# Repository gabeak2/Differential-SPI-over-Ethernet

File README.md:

# Differential-SPI-over-Ethernet
The board is meant to drive 2 SPI channels differentially over ethernet cables, and plugs into those "PMOD" connectors that all the FPGA dev boards have (but they are just 6x2 R/A 100mil headers, so also compatible with dupont/breadboard wires).  Right now I have one SPI channel with 500kHz slew-rate-limited transceivers stuffed, and one with 15MHz ones, but the chips have an identical SOIC-8 footprint so it's just a BOM change to swap them around whichever way you like.  There are solder jumpers on the board that let you hook the transceivers up so that it works for either the host side or the client side (clk is an output on a SPI host, but an input on an SPI client board).  You can also try a UART-based communication system on this board by only hooking up some of the pins - it's worth mentioning that many modern MCUs can do "UART" at over 10MHz, so theoretically if this link is just between an FPGA and one of those MCUs there are no restrictions to conventional UART baud rates, and UART would use 1/2 the pins of SPI.  Although I do love how SPI seems just made to work over RJ45 and ethernet cables!

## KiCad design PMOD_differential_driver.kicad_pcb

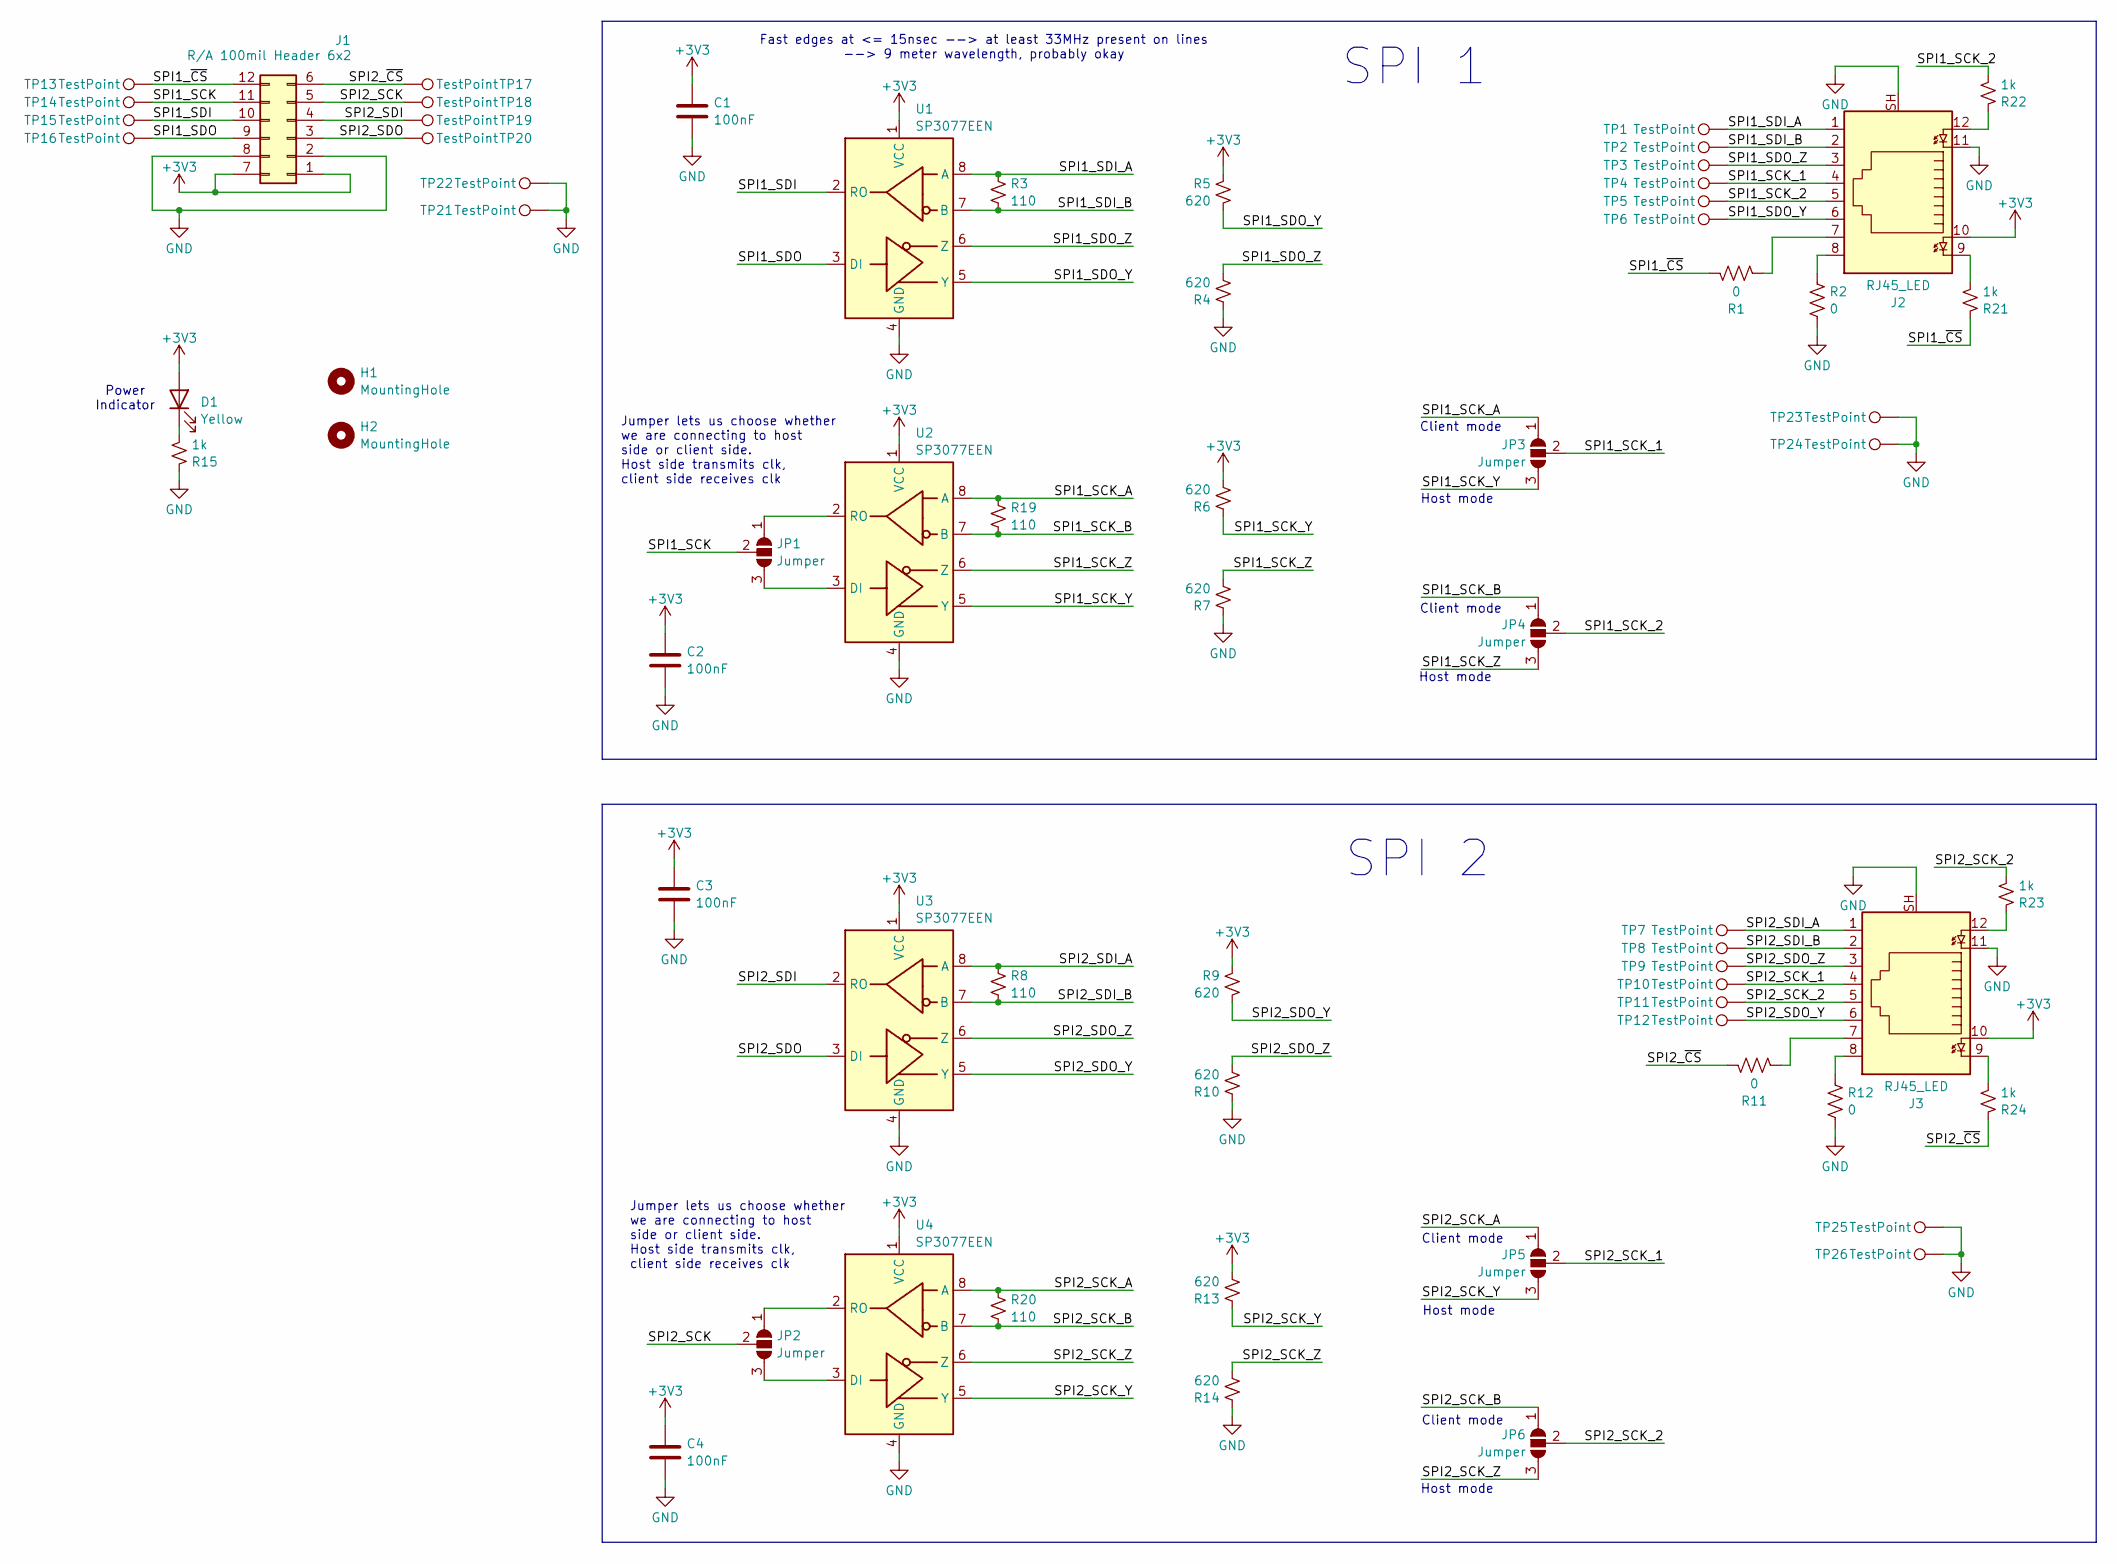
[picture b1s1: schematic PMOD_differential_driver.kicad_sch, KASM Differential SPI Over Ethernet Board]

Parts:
C1, C2, C3, C4: 100nF; C_0603_1608Metric; LCSC C14663
D1: Yellow; LED_0603_1608Metric; LCSC C72038
H1, H2: MountingHole; MountingHole_3.2mm_M3
J1: R/A 100mil Header 6x2; pmod_mating_conn; LCSC C60565
J2, J3: RJ45_LED; RJ45_Connfly_DS1128-09-S8xx-S_Horizontal; LCSC C86578
JP1, JP2, JP3, JP4, JP5, JP6: Jumper; SolderJumper-3_P1.3mm_Open_Pad1.0x1.5mm
R1, R2, R11, R12: 0; R_0603_1608Metric; LCSC C21189
R3, R8, R19, R20: 110; R_0603_1608Metric; LCSC C22781
R4, R5, R6, R7, R9, R10, R13, R14: 620; R_0603_1608Metric; LCSC C23220
R15, R21, R22, R23, R24: 1k; R_0603_1608Metric; LCSC C21190
TP1, TP2, TP3, TP4, TP5, TP6, TP7, TP8, TP9, TP10, TP11, TP12, TP13, TP14, TP15, TP16, TP17, TP18, TP19, TP20, TP21, TP22, TP23, TP24, TP25, TP26: TestPoint; PinHeader_1x01_P1.00mm_Vertical
U1, U2, U3, U4: SP3077EEN; SOIC-8_3.9x4.9mm_P1.27mm; LCSC C916162

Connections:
+3V3: C1.1, C2.1, C3.1, C4.1, D1.2 (A), J1.1, J1.7, J2.10, J3.10, R5.2, R6.2, R9.2, R13.2, U1.1 (VCC), U2.1 (VCC), U3.1 (VCC), U4.1 (VCC)
/SPI1_SCK: J1.11, JP1.2 (C), TP14.1
/SPI1_SCK_1: J2.4, JP3.2 (C), TP4.1
/SPI1_SCK_2: J2.5, JP4.2 (C), R22.2, TP5.1
/SPI1_SCK_A: JP3.1 (A), R19.1, U2.8 (A)
/SPI1_SCK_B: JP4.1 (A), R19.2, U2.7 (B)
/SPI1_SCK_Y: JP3.3 (B), R6.1, U2.5 (Y)
/SPI1_SCK_Z: JP4.3 (B), R7.2, U2.6 (Z)
/SPI1_SDI: J1.10, TP15.1, U1.2 (RO)
/SPI1_SDI_A: J2.1, R3.1, TP1.1, U1.8 (A)
/SPI1_SDI_B: J2.2, R3.2, TP2.1, U1.7 (B)
/SPI1_SDO: J1.9, TP16.1, U1.3 (DI)
/SPI1_SDO_Y: J2.6, R5.1, TP6.1, U1.5 (Y)
/SPI1_SDO_Z: J2.3, R4.2, TP3.1, U1.6 (Z)
/SPI1_~CS: J1.12, R1.2, R21.1, TP13.1
/SPI2_SCK: J1.5, JP2.2 (C), TP18.1
/SPI2_SCK_1: J3.4, JP5.2 (C), TP10.1
/SPI2_SCK_2: J3.5, JP6.2 (C), R23.2, TP11.1
/SPI2_SCK_A: JP5.1 (A), R20.1, U4.8 (A)
/SPI2_SCK_B: JP6.1 (A), R20.2, U4.7 (B)
/SPI2_SCK_Y: JP5.3 (B), R13.1, U4.5 (Y)
/SPI2_SCK_Z: JP6.3 (B), R14.2, U4.6 (Z)
/SPI2_SDI: J1.4, TP19.1, U3.2 (RO)
/SPI2_SDI_A: J3.1, R8.1, TP7.1, U3.8 (A)
/SPI2_SDI_B: J3.2, R8.2, TP8.1, U3.7 (B)
/SPI2_SDO: J1.3, TP20.1, U3.3 (DI)
/SPI2_SDO_Y: J3.6, R9.1, TP12.1, U3.5 (Y)
/SPI2_SDO_Z: J3.3, R10.2, TP9.1, U3.6 (Z)
/SPI2_~CS: J1.6, R11.2, R24.1, TP17.1
GND: C1.2, C2.2, C3.2, C4.2, J1.2, J1.8, J2.11, J2.SH, J3.11, J3.SH, R2.1, R4.1, R7.1, R10.1, R12.1, R14.1, R15.1, TP21.1, TP22.1, TP23.1, TP24.1, TP25.1, TP26.1, U1.4 (GND), U2.4 (GND), U3.4 (GND), U4.4 (GND)
unnamed: D1.1 (K), R15.2
unnamed: J2.7, R1.1
unnamed: J2.8, R2.2
unnamed: J2.9, R21.2
unnamed: J2.12, R22.1
unnamed: J3.7, R11.1
unnamed: J3.8, R12.2
unnamed: J3.9, R24.2
unnamed: J3.12, R23.1
unnamed: JP1.1 (A), U2.2 (RO)
unnamed: JP1.3 (B), U2.3 (DI)
unnamed: JP2.1 (A), U4.2 (RO)
unnamed: JP2.3 (B), U4.3 (DI)

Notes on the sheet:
SPI 1
SPI 2
Client mode
Host mode
Fast edges at <= 15nsec --> at least 33MHz present on lines --> 9 meter wavelength, probably okay
Power Indicator
Jumper lets us choose whether we are connecting to host side or client side. Host side transmits clk, client side receives clk

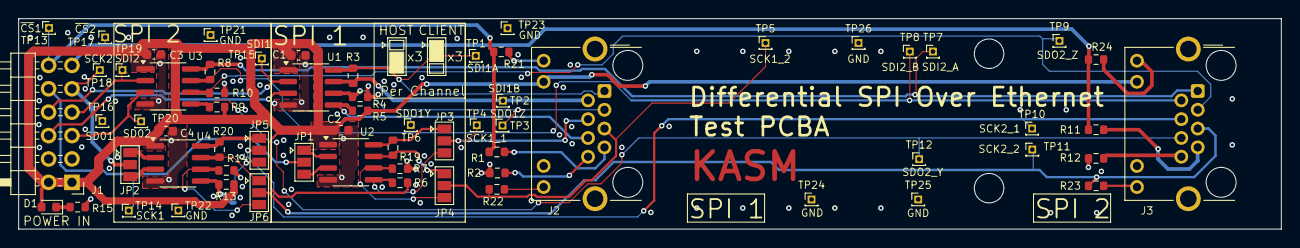
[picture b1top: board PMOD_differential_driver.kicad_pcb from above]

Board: 4 copper layers, 137.2 x 22.9 mm, 67 parts (0 on the bottom side), 43 nets.

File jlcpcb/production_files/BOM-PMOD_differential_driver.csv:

Comment,Designator,Footprint,LCSC
100nF,"C1,C2,C3,C4",C_0603_1608Metric,C14663
0,"R1,R11,R12,R2",R_0603_1608Metric,C21189
1k,"R15,R21,R22,R23,R24",R_0603_1608Metric,C21190
110,"R19,R20,R3,R8",R_0603_1608Metric,C22781
620,"R10,R13,R14,R4,R5,R6,R7,R9",R_0603_1608Metric,C23220
R/A 100mil Header 6x2,J1,pmod_mating_conn,C60565
Yellow,D1,LED_0603_1608Metric,C72038
RJ45_LED,"J2,J3",RJ45_Connfly_DS1128-09-S8xx-S_Horizontal,C86578
SP3078EEN,"U1,U2,U3,U4",SOIC-8_3.9x4.9mm_P1.27mm,C95362
TestPoint,TP19,PinHeader_1x01_P1.00mm_Vertical,
TestPoint,TP13,PinHeader_1x01_P1.00mm_Vertical,
TestPoint,TP15,PinHeader_1x01_P1.00mm_Vertical,
TestPoint,TP10,PinHeader_1x01_P1.00mm_Vertical,
TestPoint,TP26,PinHeader_1x01_P1.00mm_Vertical,
TestPoint,TP17,PinHeader_1x01_P1.00mm_Vertical,
TestPoint,TP25,PinHeader_1x01_P1.00mm_Vertical,
TestPoint,TP1,PinHeader_1x01_P1.00mm_Vertical,
TestPoint,TP4,PinHeader_1x01_P1.00mm_Vertical,
TestPoint,TP3,PinHeader_1x01_P1.00mm_Vertical,
TestPoint,TP18,PinHeader_1x01_P1.00mm_Vertical,
TestPoint,TP24,PinHeader_1x01_P1.00mm_Vertical,
TestPoint,TP5,PinHeader_1x01_P1.00mm_Vertical,
TestPoint,TP12,PinHeader_1x01_P1.00mm_Vertical,
TestPoint,TP9,PinHeader_1x01_P1.00mm_Vertical,
TestPoint,TP2,PinHeader_1x01_P1.00mm_Vertical,
TestPoint,TP21,PinHeader_1x01_P1.00mm_Vertical,
TestPoint,TP7,PinHeader_1x01_P1.00mm_Vertical,
TestPoint,TP14,PinHeader_1x01_P1.00mm_Vertical,
TestPoint,TP6,PinHeader_1x01_P1.00mm_Vertical,
TestPoint,TP23,PinHeader_1x01_P1.00mm_Vertical,
TestPoint,TP8,PinHeader_1x01_P1.00mm_Vertical,
TestPoint,TP16,PinHeader_1x01_P1.00mm_Vertical,
TestPoint,TP22,PinHeader_1x01_P1.00mm_Vertical,
TestPoint,TP20,PinHeader_1x01_P1.00mm_Vertical,
TestPoint,TP11,PinHeader_1x01_P1.00mm_Vertical,
